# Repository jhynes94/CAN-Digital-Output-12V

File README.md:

# CAN-Digital-Output-12V
CAN controlled Digital Outputs providing 12V power with __ Current each.

## Items to complete
1. Detemine MOSFET to use for design (based on Current(A)/Costs constraints).
2. Design better interface board to use Arduino Nano Programmer
    1. JST Connector to Arduino Development Board
    2. 2.54mm Connector with standard interface board
    3. Consider adding UART connector as well.
3. Determine modes needed for device
    1. CAN ID changing?
    2. CAN Mode changing?
    3. How this should be modified? (DIP swich or via SW)

## Development Setup

Programming the ATTiny is a bit difficult. Setup can be completed using the following tutorial:
https://youtu.be/AL9vK_xMt4E

The library used for SPI enabled CAN device:
https://github.com/autowp/arduino-mcp2515

PEAK CAN usb device is used for interfacing and development. The software to run this is called <b>pcanview<b>

## Far Future items

Future Tutorial for programming an alternative way:
https://www.youtube.com/watch?v=ra7bT74EGUs

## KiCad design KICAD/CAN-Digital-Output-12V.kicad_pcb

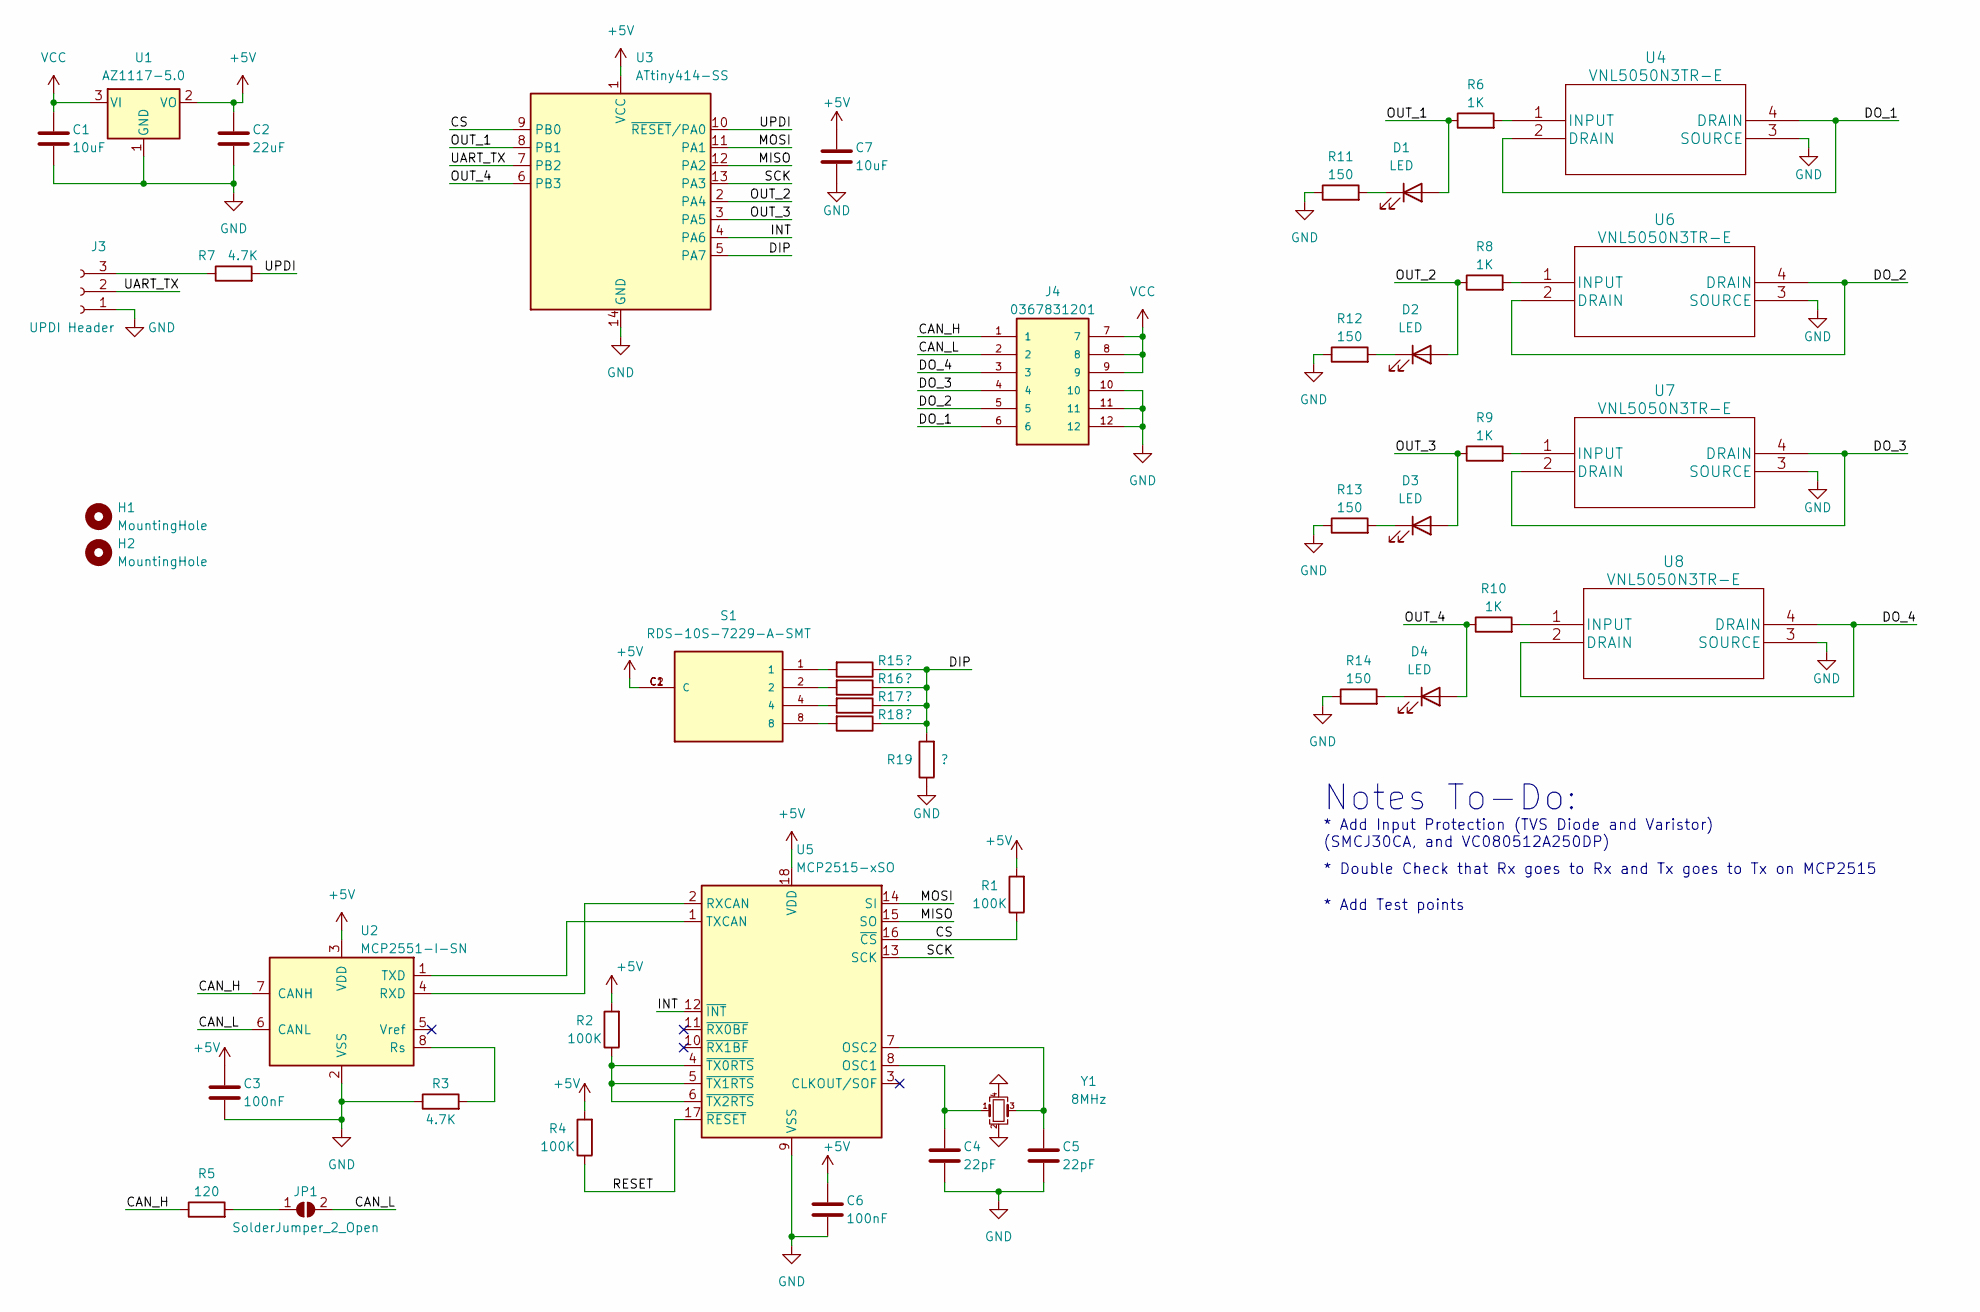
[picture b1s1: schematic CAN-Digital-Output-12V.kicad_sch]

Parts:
C1, C7: 10uF; C_0805_2012Metric_Pad1.18x1.45mm_HandSolder; Manufacturer PN CL21A106KOQNNNE; Digi-Key PN 1276-1096-2-ND
C2: 22uF; C_0805_2012Metric_Pad1.18x1.45mm_HandSolder; Manufacturer PN CL21A226MOCLRNC; Digi-Key PN 1276-6780-1-ND
C3, C6: 100nF; C_0603_1608Metric_Pad1.08x0.95mm_HandSolder; Manufacturer PN CL10B104KB8NNNC; Digi-Key PN 1276-1000-1-ND
C4, C5: 22pF; C_0603_1608Metric_Pad1.08x0.95mm_HandSolder; Manufacturer PN CC0603JRNPO9BN220; Digi-Key PN 311-1062-1-ND
D1, D2, D3, D4: LED; LED_0603_1608Metric_Pad1.05x0.95mm_HandSolder; Manufacturer PN LTST-C191KGKT; Digi-Key PN 160-1446-1-ND
H1, H2: MountingHole; MountingHole_2.2mm_M2_ISO14580
J3: UPDI Header; PinHeader_1x03_P1.27mm_Vertical
J4: 0367831201; MOLEX_0367831201; PARTREV F1; Digi-Key PN WM9330-ND
JP1: SolderJumper_2_Open; SolderJumper-2_P1.3mm_Open_TrianglePad1.0x1.5mm
R1, R2, R4: 100K; R_0603_1608Metric_Pad0.98x0.95mm_HandSolder; Manufacturer PN RC0603FR-07100KL; Digi-Key PN 311-100KHRCT-ND
R3, R7: 4.7K; R_0603_1608Metric_Pad0.98x0.95mm_HandSolder; Manufacturer PN RC0402JR-074K7L; Digi-Key PN 311-4.7KJRCT-ND
R5: 120; R_1206_3216Metric_Pad1.30x1.75mm_HandSolder; Manufacturer PN AC1206FR-07120RL; Digi-Key PN YAG3810CT-ND
R6, R8, R9, R10: 1K; R_0603_1608Metric_Pad0.98x0.95mm_HandSolder; Manufacturer PN RC0603FR-071KL; Digi-Key PN 311-1.00KHRCT-ND
R11, R12, R13, R14: 150; R_0603_1608Metric_Pad0.98x0.95mm_HandSolder; Manufacturer PN RC0603FR-07150RL; Digi-Key PN 311-150HRCT-ND
R15, R16, R17, R18, R19: ?; R_0603_1608Metric_Pad0.98x0.95mm_HandSolder
S1: RDS-10S-7229-A-SMT; SW_RDS-10S-7229-A-SMT; PARTREV 1.0; Digi-Key PN 2223-RDS-10S-7229-A-SMT-ND
U1: AZ1117-5.0; SOT-223-3_TabPin2; Manufacturer PN AZ1117IH-5.0TRG1; Digi-Key PN AZ1117IH-5.0TRG1DICT-ND
U2: MCP2551-I-SN; SOIC-8_3.9x4.9mm_P1.27mm; Manufacturer PN MCP2551-I/SN; Digi-Key PN MCP2551-I/SN-ND
U3: ATtiny414-SS; SOIC-14_3.9x8.7mm_P1.27mm; Manufacturer PN ATTINY414-SSNR; Digi-Key PN ATTINY414-SSNRCT-ND
U4, U6, U7, U8: VNL5050N3TR-E; SOT-223; Manufacturer PN VNL5050N3TR-E; Digi-Key PN 497-11709-1-ND
U5: MCP2515-xSO; SOIC-18W_7.5x11.6mm_P1.27mm; Manufacturer PN MCP2515-I/SO; Digi-Key PN MCP2515-I/SO-ND
Y1: 8MHz; Crystal_SMD_3225-4Pin_3.2x2.5mm_HandSoldering; Manufacturer PN ECS-80-8-33-JEN-TR3; Digi-Key PN 50-ECS-80-8-33-JEN-TR3CT-ND

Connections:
+5V: C2.1, C3.1, C6.1, C7.1, R1.2, R2.2, R4.2, S1.C1 (C), S1.C2 (C), U1.2 (VO), U2.3 (VDD), U3.1 (VCC), U5.18 (VDD)
/CAN_H: J4.1, R5.1, U2.7 (CANH)
/CAN_L: J4.2, JP1.2 (B), U2.6 (CANL)
/CS: R1.1, U3.9 (PB0), U5.16 (~CS)
/DIP: R15.1, R16.1, R17.1, R18.1, R19.2, U3.5 (PA7)
/DO_1: J4.6, U4.2 (DRAIN), U4.4 (DRAIN)
/DO_2: J4.5, U6.2 (DRAIN), U6.4 (DRAIN)
/DO_3: J4.4, U7.2 (DRAIN), U7.4 (DRAIN)
/DO_4: J4.3, U8.2 (DRAIN), U8.4 (DRAIN)
/INT: U3.4 (PA6), U5.12 (~INT)
/MISO: U3.12 (PA2), U5.15 (SO)
/MOSI: U3.11 (PA1), U5.14 (SI)
/OUT_1: D1.2 (A), R6.1, U3.8 (PB1)
/OUT_2: D2.2 (A), R8.1, U3.2 (PA4)
/OUT_3: D3.2 (A), R9.1, U3.3 (PA5)
/OUT_4: D4.2 (A), R10.1, U3.6 (PB3)
/RESET: R4.1, U5.17 (~RESET)
/SCK: U3.13 (PA3), U5.13 (SCK)
/UART_TX: J3.2, U3.7 (PB2)
/UPDI: R7.2, U3.10 (~RESET/PA0)
GND: C1.2, C2.2, C3.2, C4.2, C5.2, C6.2, C7.2, J3.1, J4.10, J4.11, J4.12, R3.1, R11.1, R12.1, R13.1, R14.1, R19.1, U1.1 (GND), U2.2 (VSS), U3.14 (GND), U4.3 (SOURCE), U5.9 (VSS), U6.3 (SOURCE), U7.3 (SOURCE), U8.3 (SOURCE), Y1.2, Y1.4
unnamed: C4.1, U5.8 (OSC1), Y1.1
unnamed: C5.1, U5.7 (OSC2), Y1.3
unnamed: D1.1 (K), R11.2
unnamed: D2.1 (K), R12.2
unnamed: D3.1 (K), R13.2
unnamed: D4.1 (K), R14.2
unnamed: J3.3, R7.1
unnamed: JP1.1 (A), R5.2
unnamed: R2.1, U5.4 (~TX0RTS), U5.5 (~TX1RTS), U5.6 (~TX2RTS)
unnamed: R3.2, U2.8 (Rs)
unnamed: R6.2, U4.1 (INPUT)
unnamed: R8.2, U6.1 (INPUT)
unnamed: R9.2, U7.1 (INPUT)
unnamed: R10.2, U8.1 (INPUT)
unnamed: R15.2, S1.1
unnamed: R16.2, S1.2
unnamed: R17.2, S1.4
unnamed: R18.2, S1.8
unnamed: U2.1 (TXD), U5.1 (TXCAN)
unnamed: U2.4 (RXD), U5.2 (RXCAN)
VCC: C1.1, J4.7, J4.8, J4.9, U1.3 (VI)

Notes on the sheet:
* Add Input Protection (TVS Diode and Varistor) (SMCJ30CA, and VC080512A250DP)
* Double Check that Rx goes to Rx and Tx goes to Tx on MCP2515
Notes To-Do:
* Add Test points

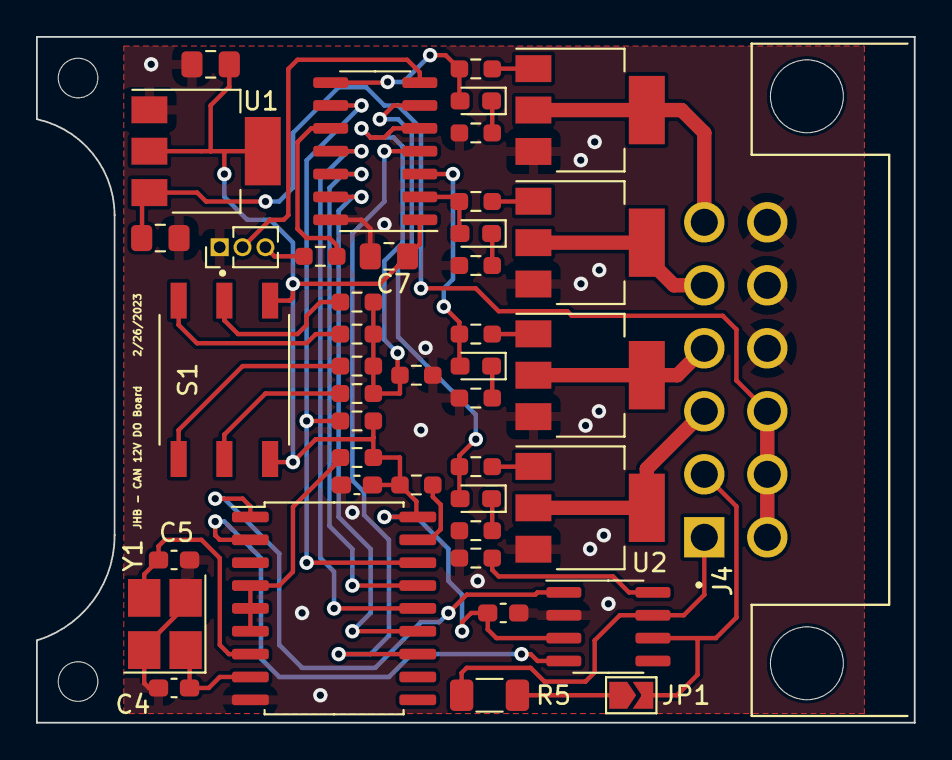
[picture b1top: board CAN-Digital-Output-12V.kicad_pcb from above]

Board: 2 copper layers, 48.8 x 38.1 mm, 45 parts (0 on the bottom side), 42 nets.

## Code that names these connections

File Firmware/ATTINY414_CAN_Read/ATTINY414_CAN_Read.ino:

#include <SPI.h>
#include <mcp2515.h>

#define OUT_1 6
#define OUT_2 0
#define OUT_3 1
#define OUT_4 4

bool blink_Out_1 = false
bool blink_Out_2 = false
bool blink_Out_3 = false
bool blink_Out_4 = false

struct can_frame canMsg;
MCP2515 mcp2515(7);

unsigned int device_CAN_ID = 1;

void setup() {
  
  mcp2515.reset();
  mcp2515.setBitrate(CAN_125KBPS, MCP_8MHZ);
  mcp2515.setNormalMode();

  //Setup Digital Outputs
  pinMode(OUT_1, OUTPUT);
  pinMode(OUT_2, OUTPUT);
  pinMode(OUT_3, OUTPUT);
  pinMode(OUT_4, OUTPUT);
}

void loop() {

  if (mcp2515.readMessage(&canMsg) == MCP2515::ERROR_OK) {
      
    //If it is the correct CAN ID
    if(canMsg.can_id == device_CAN_ID){
      
      unsigned int mask = 0b00000010;
      if((canMsg.data[0]&mask) != 0){
        digitalWrite(OUT_1, HIGH);
      }
      else {
        digitalWrite(OUT_1, LOW);
      }
      
      /*
      //Iterates Through Data    
      for (int i = 0; i<canMsg.can_dlc; i++) {
        //canMsg.data[i],HEX);
      }
      */
    }
  }
}

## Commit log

2023-02-23 First major commit
2023-02-23 Design review with Jarrod
2023-02-24 Third Design Review
2023-02-24 V1 Schematic and Placement Design complete
2023-02-26 Added rotary switch
2023-02-27 Sent to Fab
2023-03-22 V1 Software is fully functional
